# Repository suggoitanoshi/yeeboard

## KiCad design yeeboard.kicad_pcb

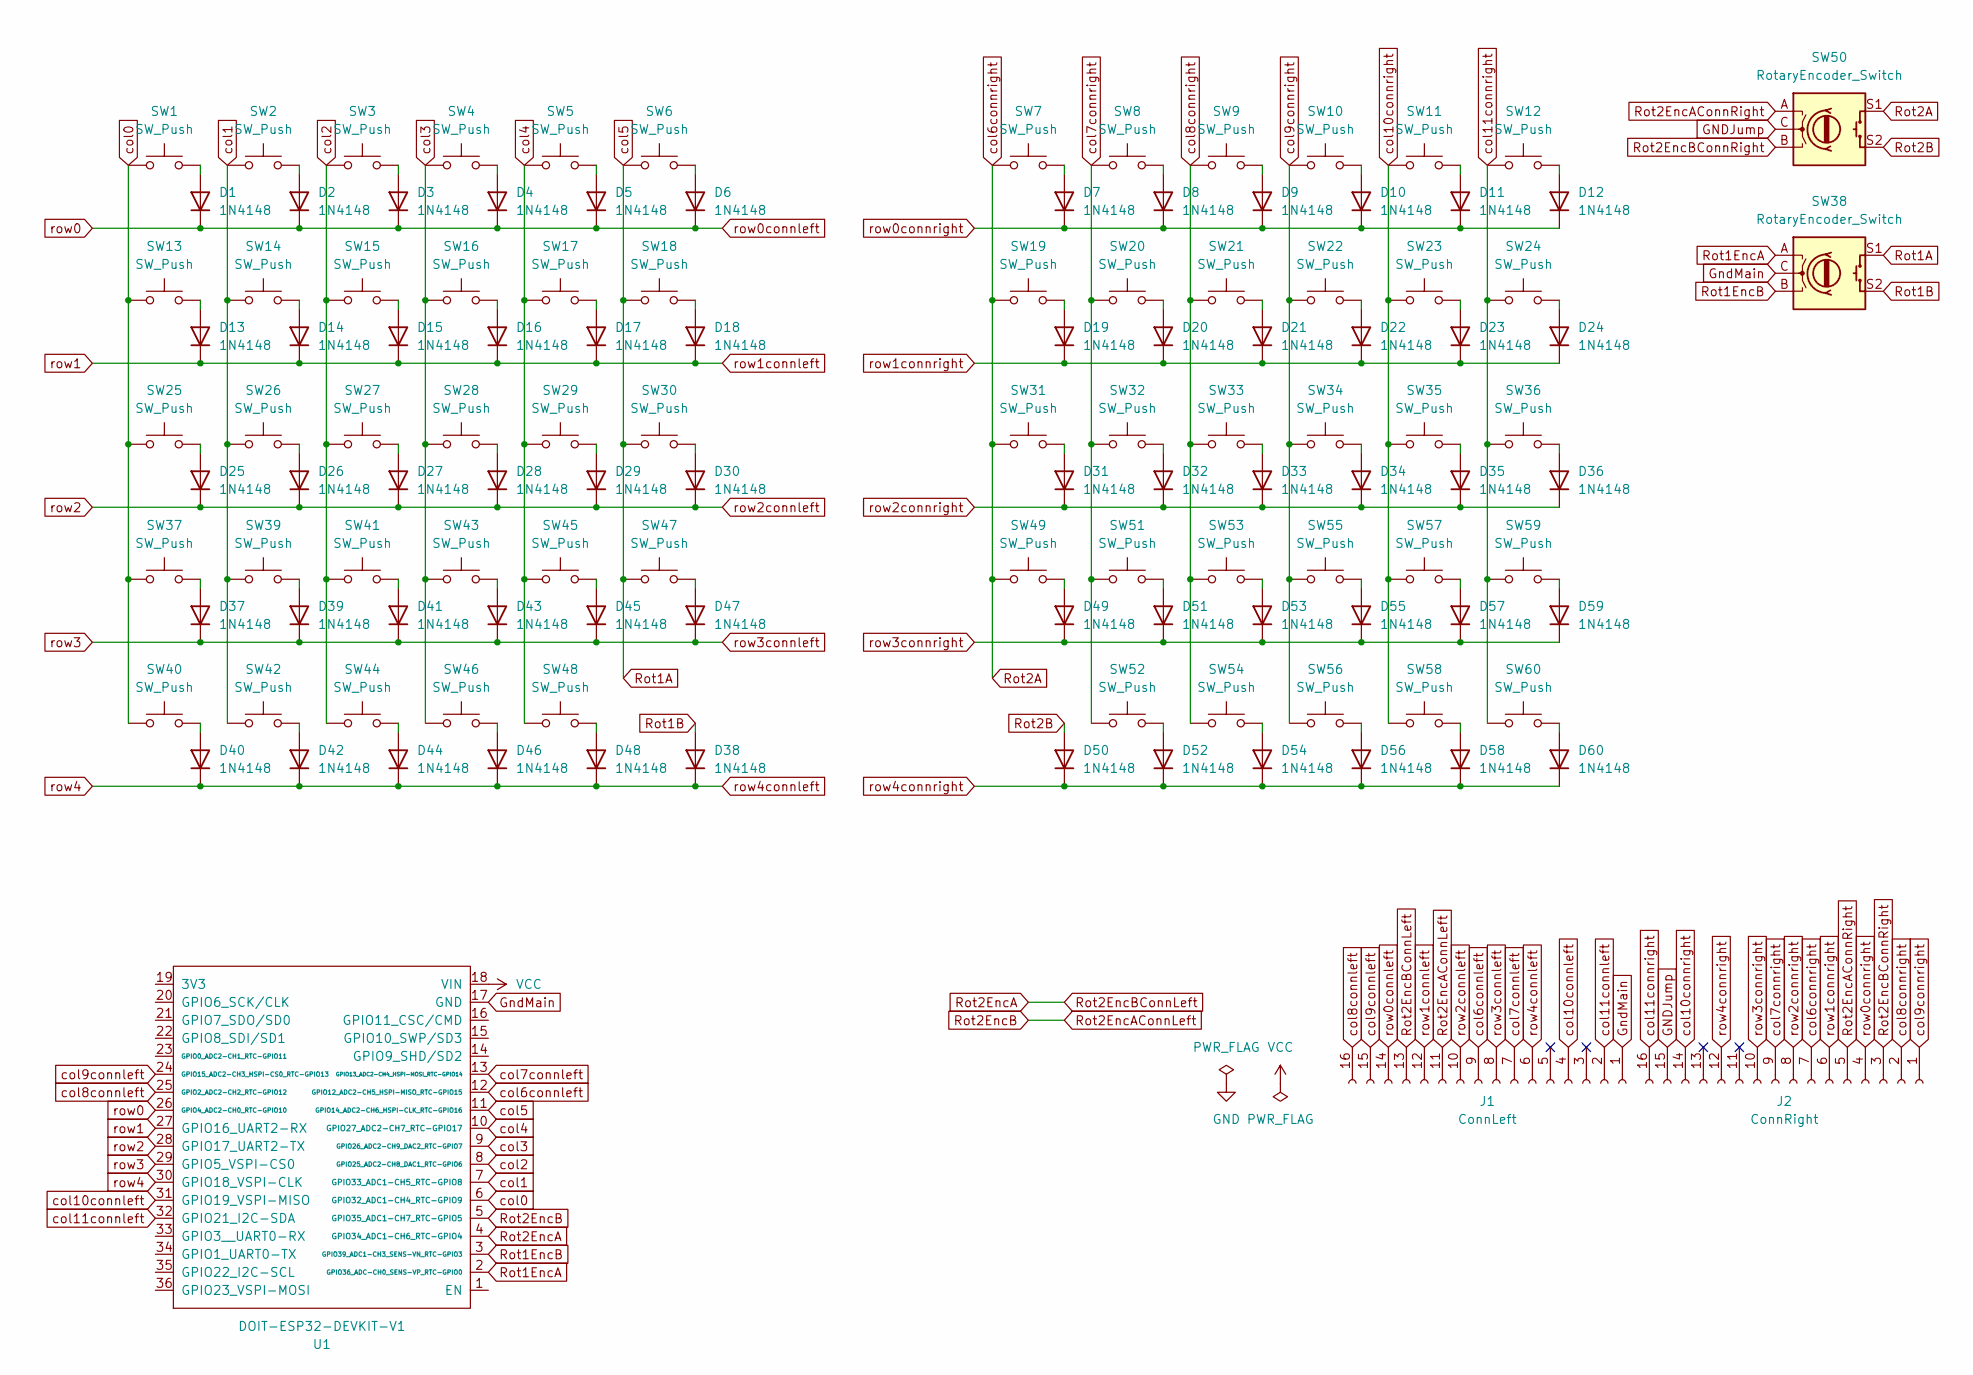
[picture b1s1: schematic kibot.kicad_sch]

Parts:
D1, D2, D3, D4, D5, D6, D7, D8, D9, D10, D11, D12, D13, D14, D15, D16, D17, D18, D19, D20, D21, D22, D23, D24, D25, D26, D27, D28, D29, D30, D31, D32, D33, D34, D35, D36, D37, D38, D39, D40, D41, D42, D43, D44, D45, D46, D47, D48, D49, D50, D51, D52, D53, D54, D55, D56, D57, D58, D59, D60: 1N4148; D_DO-35_SOD27_P7.62mm_Horizontal
J1: ConnLeft; IDC-Header_2x08_P2.54mm_Vertical
J2: ConnRight; IDC-Header_2x08_P2.54mm_Vertical
SW1, SW2, SW3, SW4, SW5, SW6, SW7, SW8, SW9, SW10, SW11, SW12, SW13, SW14, SW15, SW16, SW17, SW18, SW19, SW20, SW21, SW22, SW23, SW24, SW25, SW26, SW27, SW28, SW29, SW30, SW31, SW32, SW33, SW34, SW35, SW36, SW37, SW39, SW40, SW41, SW42, SW43, SW44, SW45, SW46, SW47, SW48, SW49, SW51, SW52, SW53, SW54, SW55, SW56, SW57, SW58, SW59, SW60: SW_Push; SW_Cherry_MX_1.00u_PCB
SW38, SW50: RotaryEncoder_Switch; RotaryEncoder_Alps_EC11E-Switch_Vertical_H20mm
U1: DOIT-ESP32-DEVKIT-V1; ESP32-DOIT-DEVKIT

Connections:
GNDJump: J2.15, SW50.C
GndMain: J1.1, SW38.C, U1.17 (GND)
unnamed: D1.2 (A), SW1.2
unnamed: D2.2 (A), SW2.2
unnamed: D3.2 (A), SW3.2
unnamed: D4.2 (A), SW4.2
unnamed: D5.2 (A), SW5.2
unnamed: D6.2 (A), SW6.2
unnamed: D7.2 (A), SW7.2
unnamed: D8.2 (A), SW8.2
unnamed: D9.2 (A), SW9.2
unnamed: D10.2 (A), SW10.2
unnamed: D11.2 (A), SW11.2
unnamed: D12.2 (A), SW12.2
unnamed: D13.2 (A), SW13.2
unnamed: D14.2 (A), SW14.2
unnamed: D15.2 (A), SW15.2
unnamed: D16.2 (A), SW16.2
unnamed: D17.2 (A), SW17.2
unnamed: D18.2 (A), SW18.2
unnamed: D19.2 (A), SW19.2
unnamed: D20.2 (A), SW20.2
unnamed: D21.2 (A), SW21.2
unnamed: D22.2 (A), SW22.2
unnamed: D23.2 (A), SW23.2
unnamed: D24.2 (A), SW24.2
unnamed: D25.2 (A), SW25.2
unnamed: D26.2 (A), SW26.2
unnamed: D27.2 (A), SW27.2
unnamed: D28.2 (A), SW28.2
unnamed: D29.2 (A), SW29.2
unnamed: D30.2 (A), SW30.2
unnamed: D31.2 (A), SW31.2
unnamed: D32.2 (A), SW32.2
unnamed: D33.2 (A), SW33.2
unnamed: D34.2 (A), SW34.2
unnamed: D35.2 (A), SW35.2
unnamed: D36.2 (A), SW36.2
unnamed: D37.2 (A), SW37.2
unnamed: D39.2 (A), SW39.2
unnamed: D40.2 (A), SW40.2
unnamed: D41.2 (A), SW41.2
unnamed: D42.2 (A), SW42.2
unnamed: D43.2 (A), SW43.2
unnamed: D44.2 (A), SW44.2
unnamed: D45.2 (A), SW45.2
unnamed: D46.2 (A), SW46.2
unnamed: D47.2 (A), SW47.2
unnamed: D48.2 (A), SW48.2
unnamed: D49.2 (A), SW49.2
unnamed: D51.2 (A), SW51.2
unnamed: D52.2 (A), SW52.2
unnamed: D53.2 (A), SW53.2
unnamed: D54.2 (A), SW54.2
unnamed: D55.2 (A), SW55.2
unnamed: D56.2 (A), SW56.2
unnamed: D57.2 (A), SW57.2
unnamed: D58.2 (A), SW58.2
unnamed: D59.2 (A), SW59.2
unnamed: D60.2 (A), SW60.2
Rot1A: SW6.1, SW18.1, SW30.1, SW38.S1, SW47.1, U1.11 (GPIO14_ADC2-CH6_HSPI-CLK_RTC-GPIO16)
Rot1B: D38.2 (A), SW38.S2
Rot1EncA: SW38.A, U1.2 (GPIO36_ADC-CH0_SENS-VP_RTC-GPIO0)
Rot1EncB: SW38.B, U1.3 (GPIO39_ADC1-CH3_SENS-VN_RTC-GPIO3)
Rot2A: J2.7, SW7.1, SW19.1, SW31.1, SW49.1, SW50.S1
Rot2B: D50.2 (A), SW50.S2
Rot2EncA: J1.13, U1.4 (GPIO34_ADC1-CH6_RTC-GPIO4)
Rot2EncAConnLeft: J1.11, U1.5 (GPIO35_ADC1-CH7_RTC-GPIO5)
Rot2EncAConnRight: J2.5, SW50.A
Rot2EncBConnRight: J2.3, SW50.B
VCC: U1.18 (VIN)
col0: SW1.1, SW13.1, SW25.1, SW37.1, SW40.1, U1.6 (GPIO32_ADC1-CH4_RTC-GPIO9)
col1: SW2.1, SW14.1, SW26.1, SW39.1, SW42.1, U1.7 (GPIO33_ADC1-CH5_RTC-GPIO8)
col2: SW3.1, SW15.1, SW27.1, SW41.1, SW44.1, U1.8 (GPIO25_ADC2-CH8_DAC1_RTC-GPIO6)
col3: SW4.1, SW16.1, SW28.1, SW43.1, SW46.1, U1.9 (GPIO26_ADC2-CH9_DAC2_RTC-GPIO7)
col4: SW5.1, SW17.1, SW29.1, SW45.1, SW48.1, U1.10 (GPIO27_ADC2-CH7_RTC-GPIO17)
col6connleft: J1.9, U1.12 (GPIO12_ADC2-CH5_HSPI-MISO_RTC-GPIO15)
col7connleft: J1.7, U1.13 (GPIO13_ADC2-CH4_HSPI-MOSI_RTC-GPIO14)
col7connright: J2.9, SW8.1, SW20.1, SW32.1, SW51.1, SW52.1
col8connleft: J1.16, U1.25 (GPIO2_ADC2-CH2_RTC-GPIO12)
col8connright: J2.2, SW9.1, SW21.1, SW33.1, SW53.1, SW54.1
col9connleft: J1.15, U1.24 (GPIO15_ADC2-CH3_HSPI-CS0_RTC-GPIO13)
col9connright: J2.1, SW10.1, SW22.1, SW34.1, SW55.1, SW56.1
col10connleft: J1.4, U1.31 (GPIO19_VSPI-MISO)
col10connright: J2.14, SW11.1, SW23.1, SW35.1, SW57.1, SW58.1
col11connleft: J1.2, U1.32 (GPIO21_I2C-SDA)
col11connright: J2.16, SW12.1, SW24.1, SW36.1, SW59.1, SW60.1
row0: D1.1 (K), D2.1 (K), D3.1 (K), D4.1 (K), D5.1 (K), D6.1 (K), J1.14, U1.26 (GPIO4_ADC2-CH0_RTC-GPIO10)
row0connright: D7.1 (K), D8.1 (K), D9.1 (K), D10.1 (K), D11.1 (K), D12.1 (K), J2.4
row1: D13.1 (K), D14.1 (K), D15.1 (K), D16.1 (K), D17.1 (K), D18.1 (K), J1.12, U1.27 (GPIO16_UART2-RX)
row1connright: D19.1 (K), D20.1 (K), D21.1 (K), D22.1 (K), D23.1 (K), D24.1 (K), J2.6
row2: D25.1 (K), D26.1 (K), D27.1 (K), D28.1 (K), D29.1 (K), D30.1 (K), J1.10, U1.28 (GPIO17_UART2-TX)
row2connright: D31.1 (K), D32.1 (K), D33.1 (K), D34.1 (K), D35.1 (K), D36.1 (K), J2.8
row3: D37.1 (K), D39.1 (K), D41.1 (K), D43.1 (K), D45.1 (K), D47.1 (K), J1.8, U1.29 (GPIO5_VSPI-CS0)
row3connright: D49.1 (K), D51.1 (K), D53.1 (K), D55.1 (K), D57.1 (K), D59.1 (K), J2.10
row4: D38.1 (K), D40.1 (K), D42.1 (K), D44.1 (K), D46.1 (K), D48.1 (K), J1.6, U1.30 (GPIO18_VSPI-CLK)
row4connright: D50.1 (K), D52.1 (K), D54.1 (K), D56.1 (K), D58.1 (K), D60.1 (K), J2.12

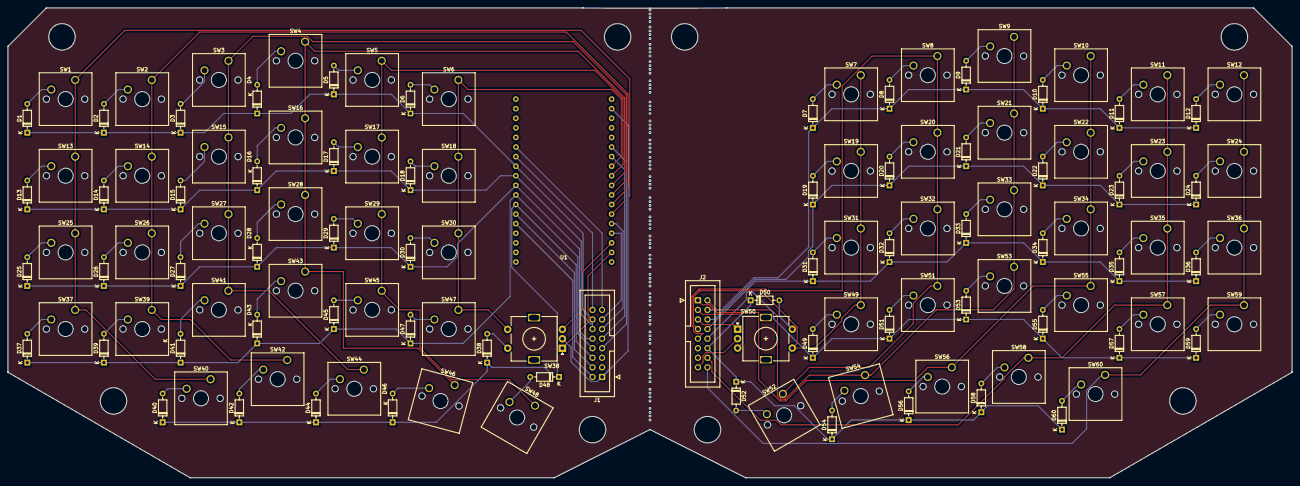
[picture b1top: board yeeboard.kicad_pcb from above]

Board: 2 copper layers, 340.5 x 124.6 mm, 145 parts (0 on the bottom side), 96 nets.

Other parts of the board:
mouse-bite-5mm-slot, mouse-bite-5mm-slot#2, mouse-bite-5mm-slot#3, mouse-bite-5mm-slot#4, mouse-bite-5mm-slot#5, mouse-bite-5mm-slot#6, mouse-bite-5mm-slot#7, mouse-bite-5mm-slot#8, mouse-bite-5mm-slot#9, mouse-bite-5mm-slot#10, mouse-bite-5mm-slot#11, mouse-bite-5mm-slot#12, mouse-bite-5mm-slot#13, mouse-bite-5mm-slot#14, mouse-bite-5mm-slot#15, mouse-bite-5mm-slot#16, mouse-bite-5mm-slot#17, mouse-bite-5mm-slot#18, mouse-bite-5mm-slot#19, mouse-bite-5mm-slot#20, mouse-bite-5mm-slot#21, mouse-bite-5mm-slot#22: VAL**; mouse-bite-long

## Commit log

2024-02-08 add plate cutout
2024-04-07 add kicad pcb design
2024-04-07 rename project
2024-04-07 update plate
2024-04-07 update prl
